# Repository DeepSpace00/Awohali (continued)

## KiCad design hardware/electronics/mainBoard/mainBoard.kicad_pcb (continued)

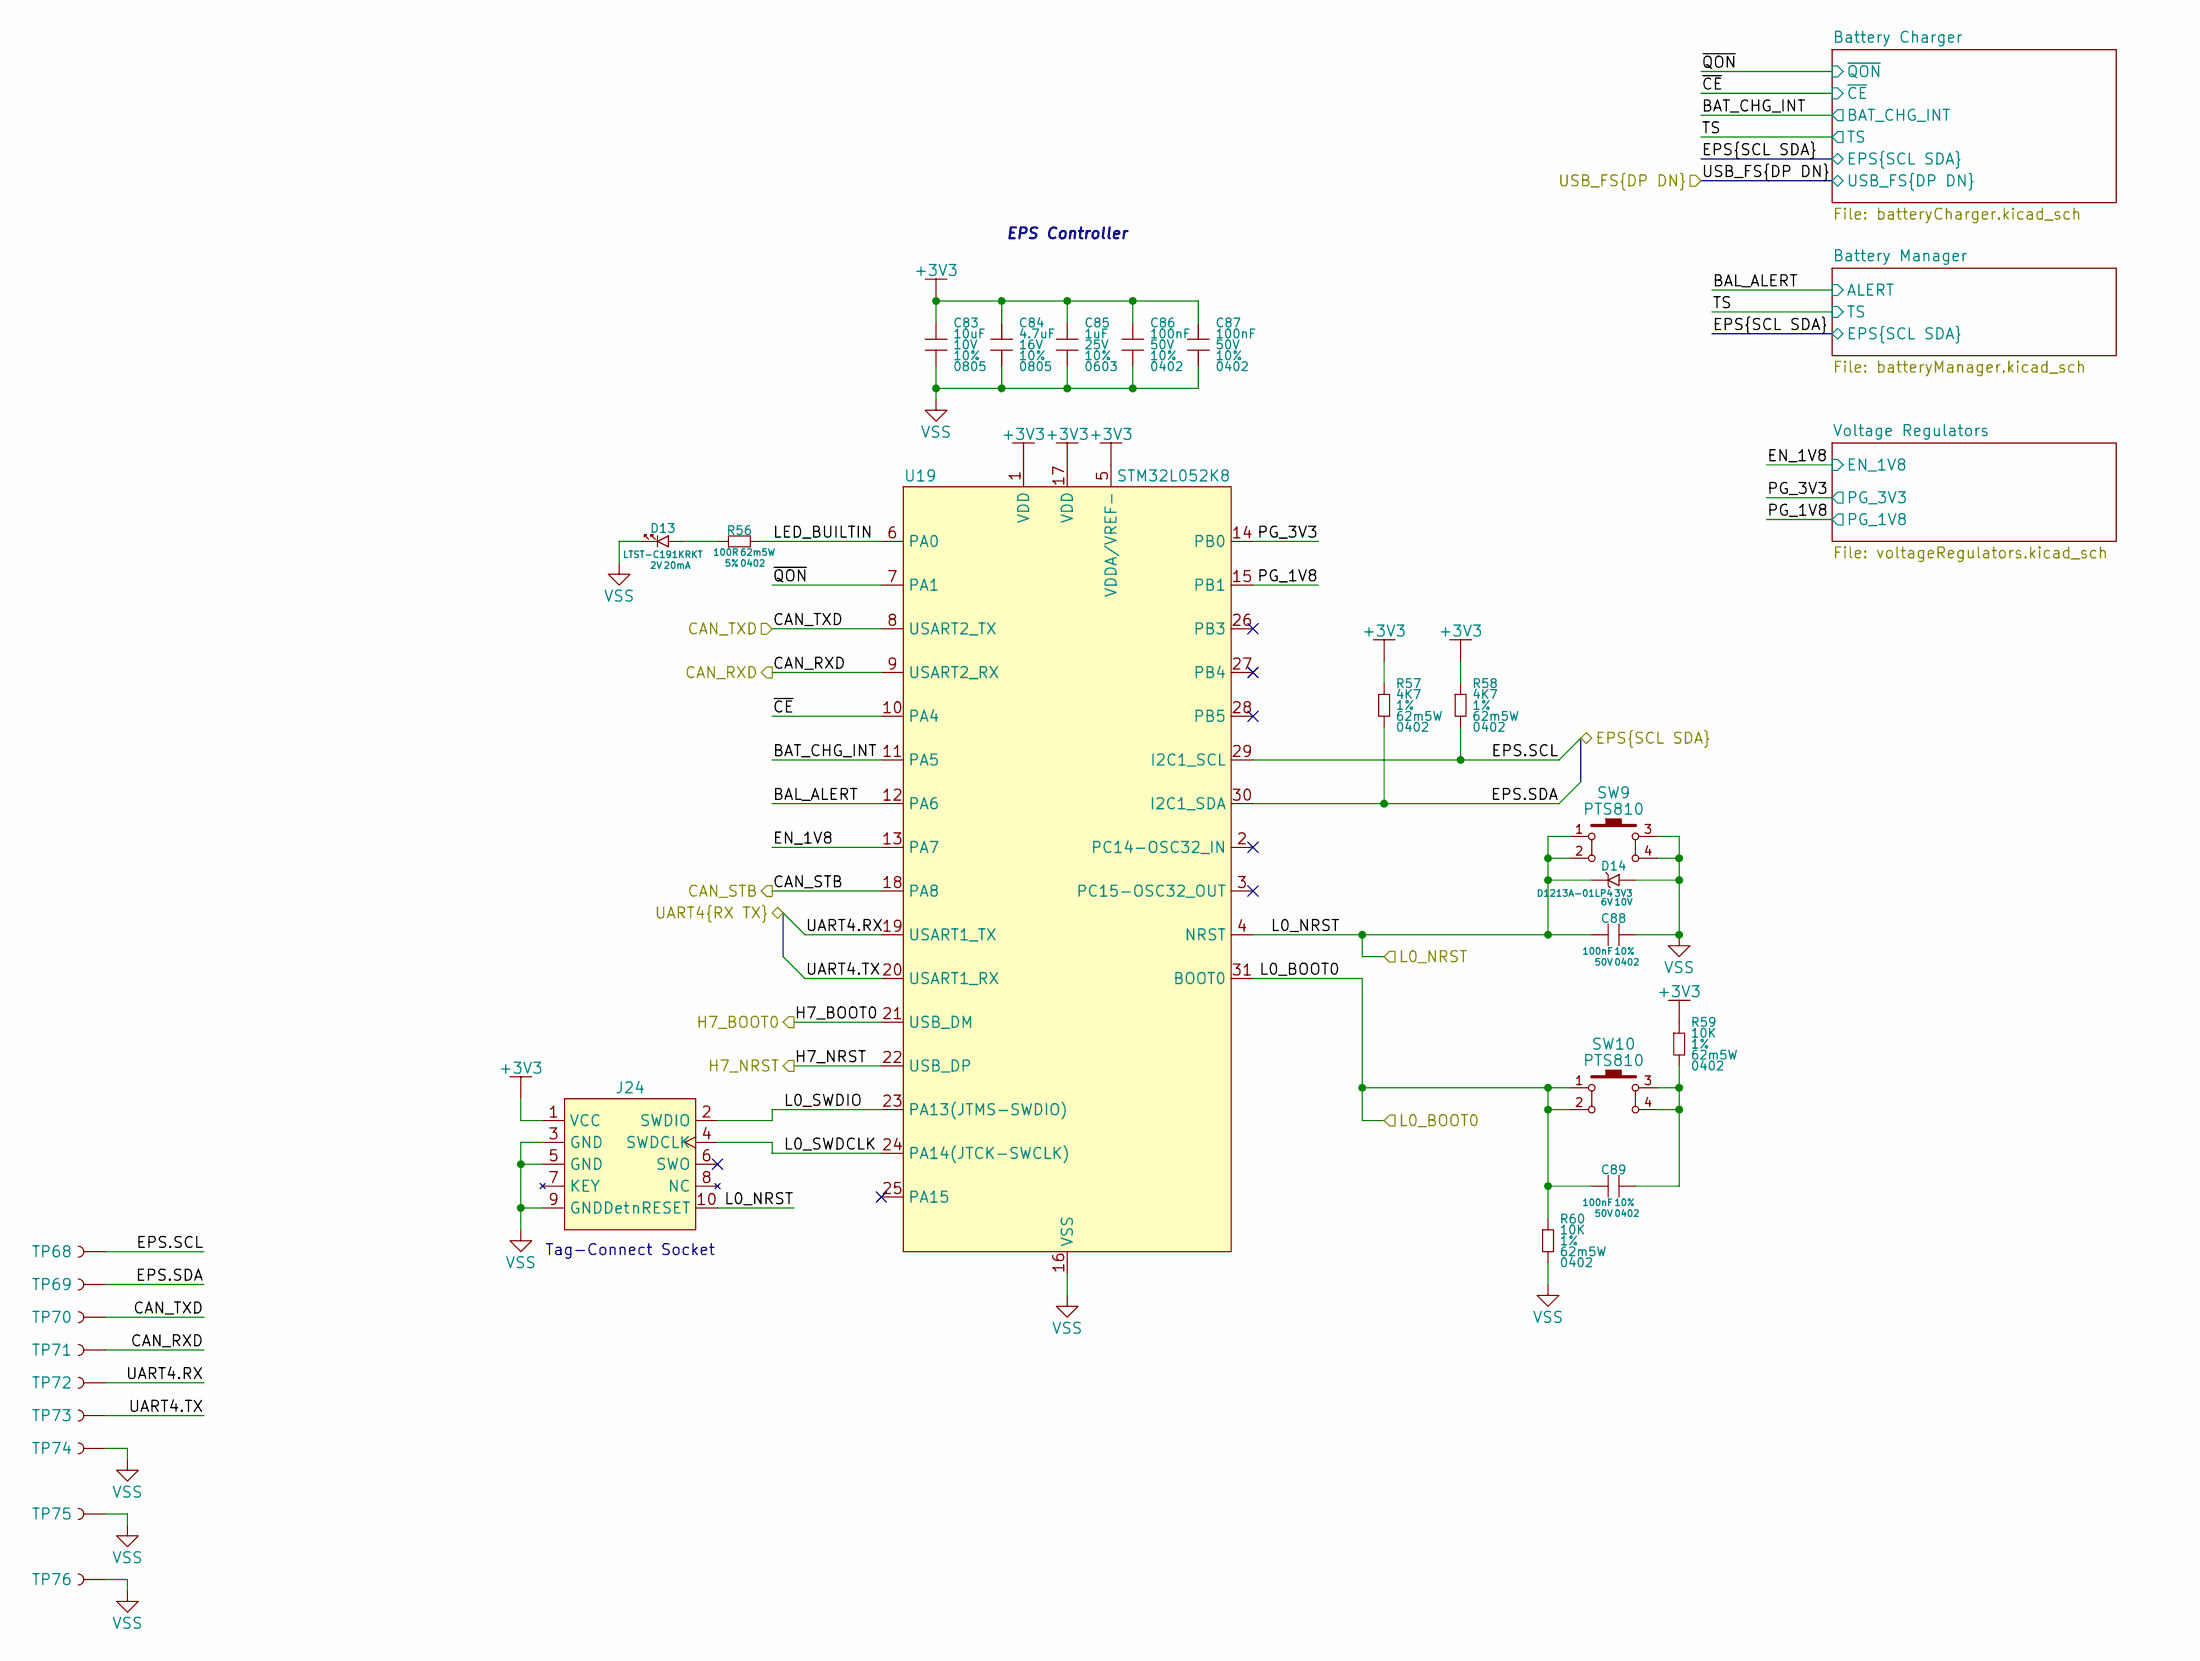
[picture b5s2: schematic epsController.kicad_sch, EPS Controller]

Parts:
C83: 10uF; GCM0805; Tolerance 10%; Voltage Rating 10V; MPN GCM21BR71A106KE22L
C84: 4.7uF; GCM0805; Tolerance 10%; Voltage Rating 16V; MPN GRT21BR71C475KE13L
C85: 1uF; GRT0603; Tolerance 10%; Voltage Rating 25V; MPN GRT188R71E105KE13D
C86, C87: 100nF; GCM0402; Tolerance 10%; Voltage Rating 50V; MPN GRT155R71H104KE01D
C88, C89: 100nF; GCM0402; Voltage Rating 50V; Tolerance 10%; MPN GRT155R71H104KE01D
D13: LTST-C191KRKT; LTST-0603; Forward Voltage 2V; MPN LTST-C191KRKT
D14: D1213A-01LP4; XDFN2P65_100X60X50L50X25L; Voltage - Reverse Stabd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 3V3; Voltage - Breakdown 6V; MPN D1213A-01LP4-7B
J24: TC2050-FP; MPN N/A
R56: 100R; CRCW0402; Tolerance 5%; Power Rating 62m5W; MPN CRCW0402100RJNED
R57, R58: 4K7; CRCW0402; Tolerance 1%; Power Rating 62m5W; MPN CRCW04024K70FKED
R59, R60: 10K; CRCW0402; Tolerance 1%; Power Rating 62m5W; MPN CRCW040210K0FKED
SW9, SW10: PTS810; MPN PTS810SJM250SMTR LFS
TP68, TP69, TP70, TP71, TP72, TP73: TP_2mm; MPN N/A
TP74, TP75, TP76: RCWCTE; TP_RCW; MPN RCWCTE
U19: STM32L052K8; UFQFPN32; MPN STM32L052K6U6TR

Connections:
+3V3: C83.1, C84.1, C85.1, C86.1, C87.1, J24.1 (VCC), R57.1, R58.1, R59.1, U19.1 (VDD), U19.5 (VDDA/VREF-), U19.17 (VDD); also elsewhere on the board
/CAN_RXD: TP71.1, U19.9 (USART2_RX); also elsewhere on the board
/CAN_STB: U19.18 (PA8); also elsewhere on the board
/CAN_TXD: TP70.1, U19.8 (USART2_TX); also elsewhere on the board
/EPS Controller/BAL_ALERT: U19.12 (PA6); also elsewhere on the board
/EPS Controller/BAT_CHG_INT: U19.11 (PA5); also elsewhere on the board
/EPS Controller/EN_1V8: U19.13 (PA7); also elsewhere on the board
/EPS Controller/H7_BOOT0: U19.21 (USB_DM); also elsewhere on the board
/EPS Controller/L0_BOOT0: C89.1, R60.1, SW10.1, SW10.2, U19.31 (BOOT0); also elsewhere on the board
/EPS Controller/L0_NRST: C88.1, D14.1, J24.10 (nRESET), SW9.1, SW9.2, U19.4 (NRST); also elsewhere on the board
/EPS Controller/L0_SWDCLK: J24.4 (SWDCLK), U19.24 (PA14(JTCK-SWCLK))
/EPS Controller/L0_SWDIO: J24.2 (SWDIO), U19.23 (PA13(JTMS-SWDIO))
/EPS Controller/LED_BUILTIN: R56.2, U19.6 (PA0)
/EPS Controller/PG_1V8: U19.15 (PB1); also elsewhere on the board
/EPS Controller/PG_3V3: U19.14 (PB0); also elsewhere on the board
/EPS Controller/UART4.RX: TP72.1, U19.19 (USART1_TX); also elsewhere on the board
/EPS Controller/UART4.TX: TP73.1, U19.20 (USART1_RX); also elsewhere on the board
/EPS Controller/~CE: U19.10 (PA4); also elsewhere on the board
/EPS Controller/~QON: U19.7 (PA1); also elsewhere on the board
/EPS.SCL: R58.2, TP68.1, U19.29 (I2C1_SCL); also elsewhere on the board
/EPS.SDA: R57.2, TP69.1, U19.30 (I2C1_SDA); also elsewhere on the board
/H7_NRST: U19.22 (USB_DP); also elsewhere on the board
unnamed: C89.2, R59.2, SW10.3, SW10.4
unnamed: D13.1, R56.1
VSS: C83.2, C84.2, C85.2, C86.2, C87.2, C88.2, D13.2, D14.2, J24.3 (GND), J24.5 (GND), J24.9 (GNDDet), R60.2, SW9.3, SW9.4, TP74.1, TP75.1, TP76.1, U19.16 (VSS), U19.32 (VSS), U19.33 (VSS); also elsewhere on the board

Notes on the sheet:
Tag-Connect Socket
EPS Controller

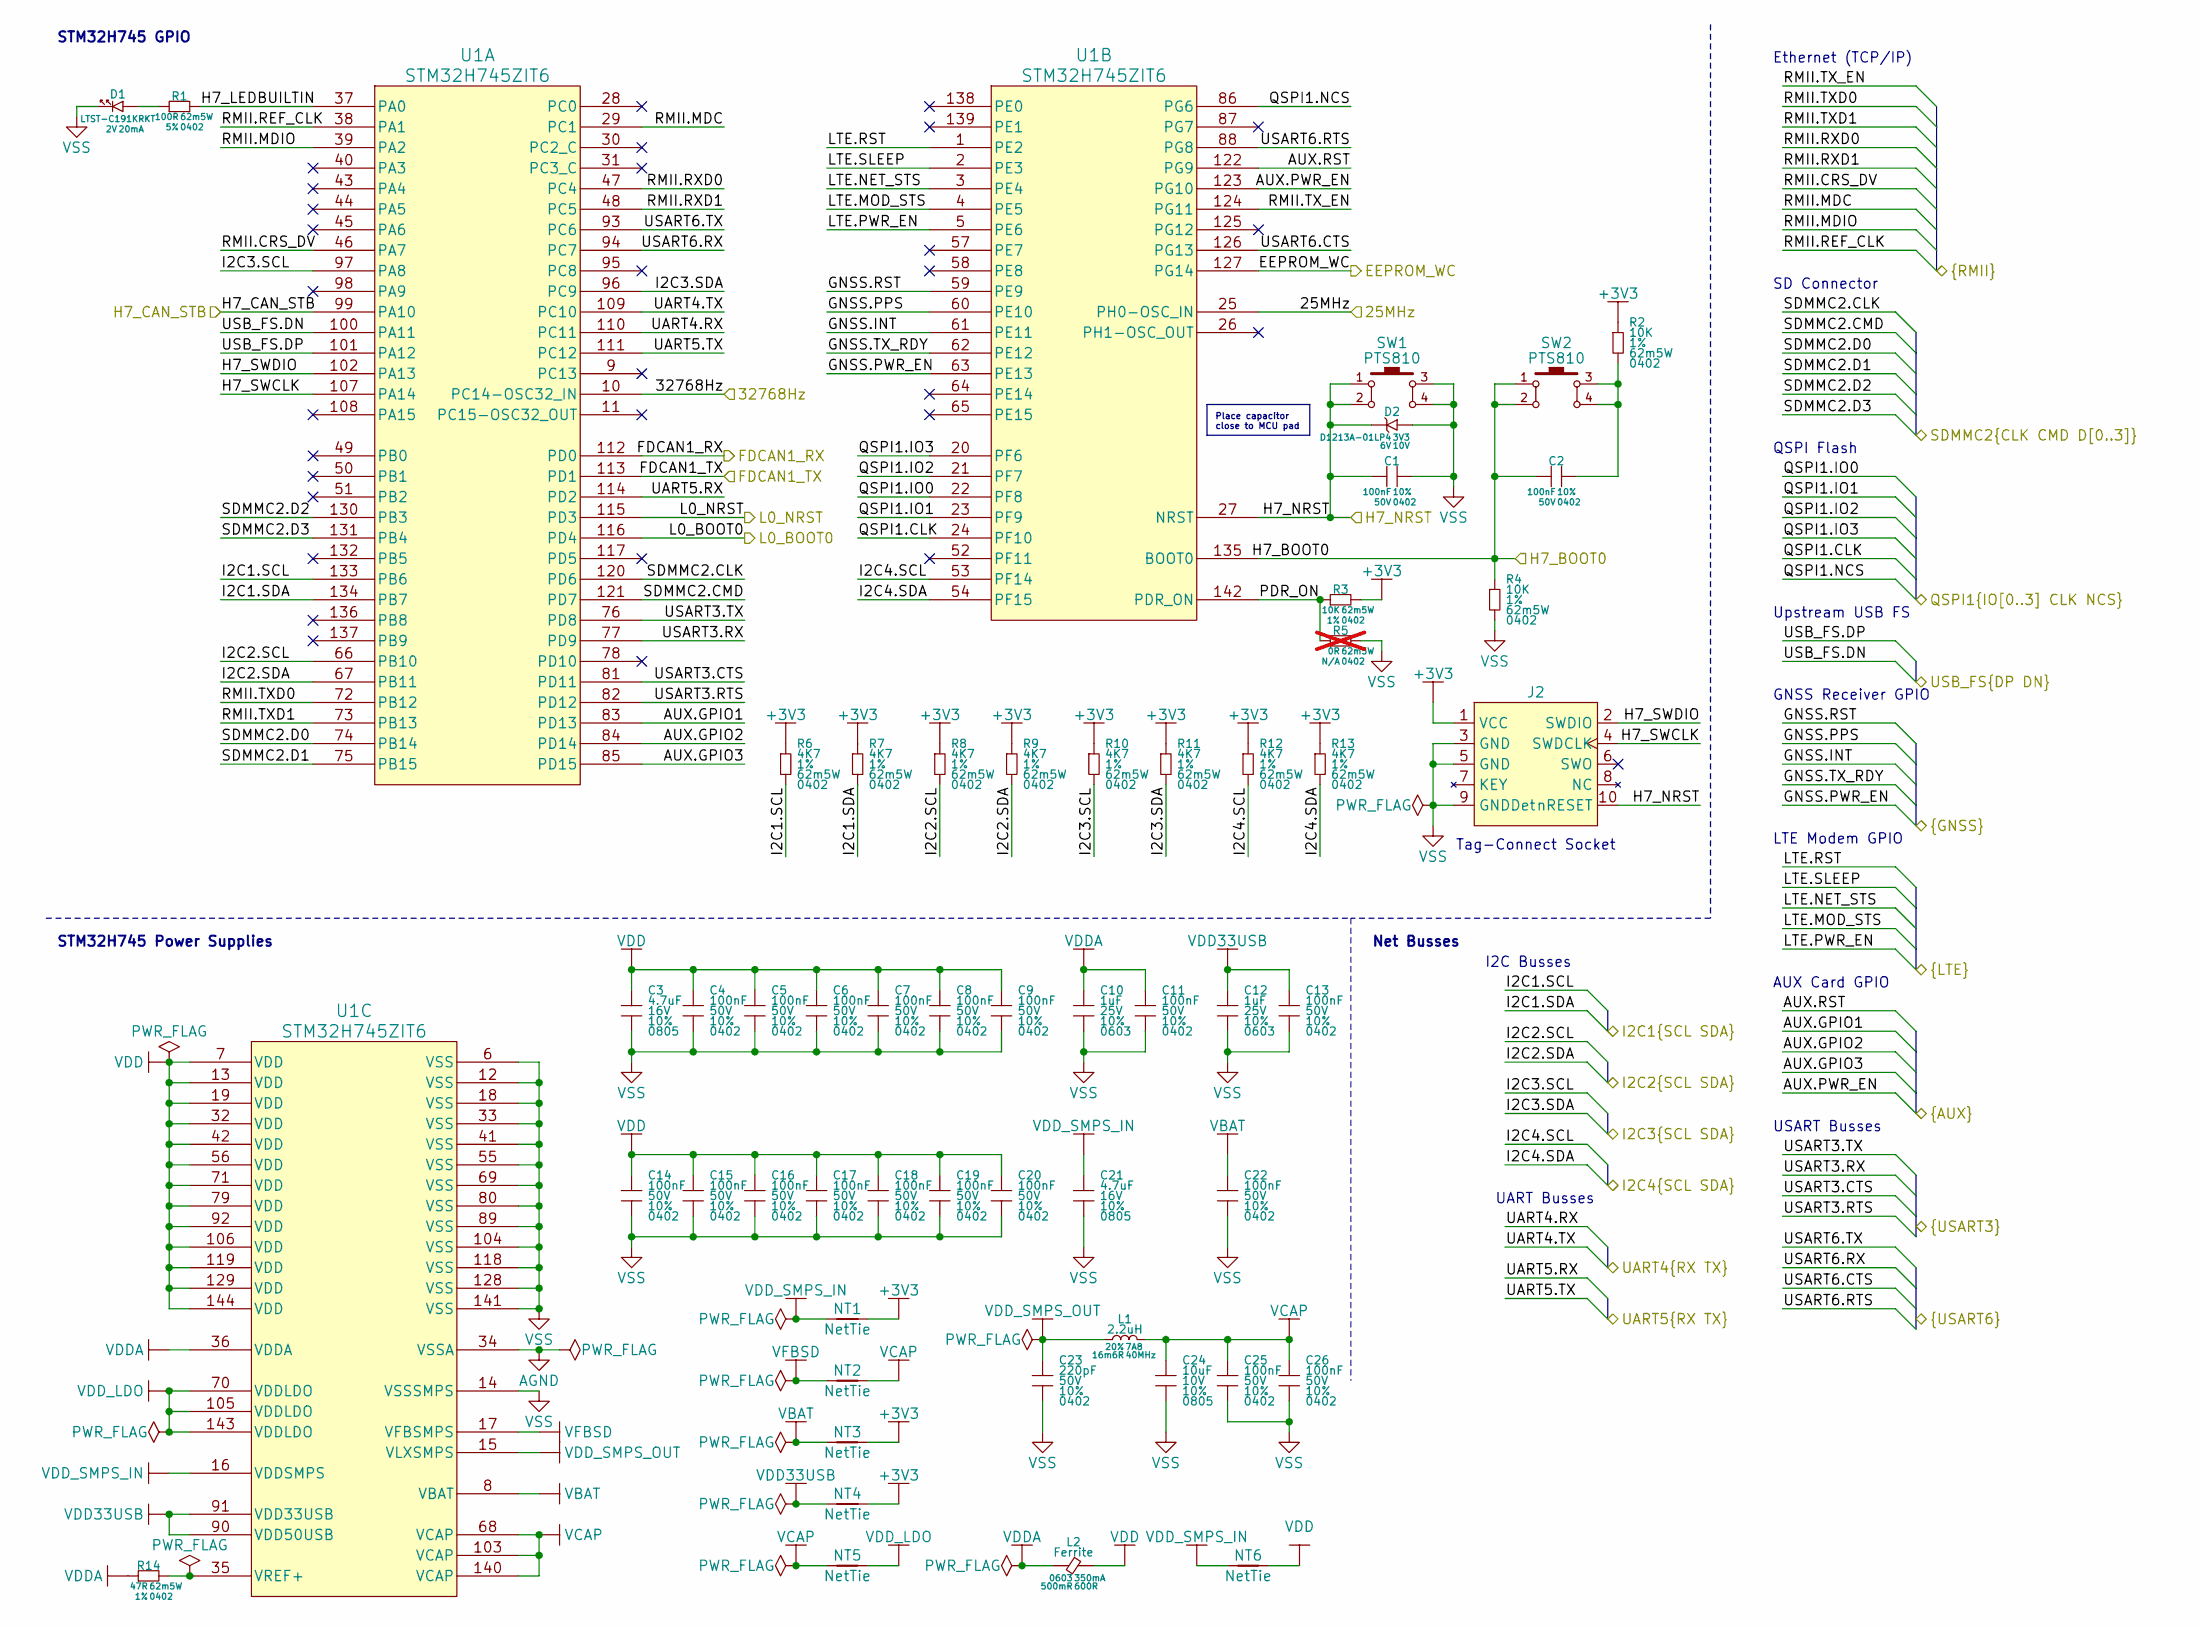
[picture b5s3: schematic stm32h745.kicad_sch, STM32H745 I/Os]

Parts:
C1, C2, C4, C5, C6, C7, C8, C9, C11, C13, C14, C15, C16, C17, C18, C19, C20, C22, C25, C26: 100nF; GCM0402; Tolerance 10%; Voltage Rating 50V; MPN GRT155R71H104KE01D
C3, C21: 4.7uF; GCM0805; Tolerance 10%; Voltage Rating 16V; MPN GRT21BR71C475KE13L
C10, C12: 1uF; GRT0603; Tolerance 10%; Voltage Rating 25V; MPN GRT188R71E105KE13D
C23: 220pF; GCM0402; Tolerance 10%; Voltage Rating 50V; MPN GRT155R71H221KE01D
C24: 10uF; GCM0805; Tolerance 10%; Voltage Rating 10V; MPN GCM21BR71A106KE22L
D1: LTST-C191KRKT; LTST-0603; Forward Voltage 2V; MPN LTST-C191KRKT
D2: D1213A-01LP4; XDFN2P65_100X60X50L50X25L; Voltage - Reverse Stabd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 3V3; Voltage - Breakdown 6V; MPN D1213A-01LP4-7B
J2: TC2050-FP; MPN N/A
L1: 2.2uH; WE-XHMI-4030; Tolerance 20%; Current Rating 7A8; MPN 74439324022
L2: Ferrite; L_0603; Current Rating 350mA; MPN MFBA3V1608K-601-R
NT1, NT2, NT3, NT4, NT5, NT6: NetTie; NetTie-2_SMD_Pad2.0mm
R1: 100R; CRCW0402; Tolerance 5%; Power Rating 62m5W; MPN CRCW0402100RJNED
R2, R3, R4: 10K; CRCW0402; Tolerance 1%; Power Rating 62m5W; MPN CRCW040210K0FKED
R5: 0R; CRCW0402; Tolerance N/A; Power Rating 62m5W; MPN CRCW04020000Z0ED; not fitted
R6, R7, R8, R9, R10, R11, R12, R13: 4K7; CRCW0402; Tolerance 1%; Power Rating 62m5W; MPN CRCW04024K70FKED
R14: 47R; CRCW0402; Tolerance 1%; Power Rating 62m5W; MPN CRCW040247R0FKED
SW1, SW2: PTS810; MPN PTS810SJM250SMTR LFS
U1: STM32H745ZIT6; LQFP-144; MPN STM32H745ZIT6

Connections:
+3V3: J2.1 (VCC), NT1.2, NT3.2, NT4.2, R2.1, R3.2, R6.1, R7.1, R8.1, R9.1, R10.1, R11.1, R12.1, R13.1; also elsewhere on the board
/Auxiliary Card/AUX.GPIO1: U1.83 (PD13); also elsewhere on the board
/Auxiliary Card/AUX.GPIO2: U1.84 (PD14); also elsewhere on the board
/Auxiliary Card/AUX.GPIO3: U1.85 (PD15); also elsewhere on the board
/Auxiliary Card/AUX.PWR_EN: U1.123 (PG10); also elsewhere on the board
/Auxiliary Card/AUX.RST: U1.122 (PG9); also elsewhere on the board
/Auxiliary Card/USART6.CTS: U1.126 (PG13); also elsewhere on the board
/Auxiliary Card/USART6.RTS: U1.88 (PG8); also elsewhere on the board
/Auxiliary Card/USART6.RX: U1.94 (PC7); also elsewhere on the board
/Auxiliary Card/USART6.TX: U1.93 (PC6); also elsewhere on the board
/CANBus Transceivers/FDCAN1_RX: U1.112 (PD0); also elsewhere on the board
/CANBus Transceivers/FDCAN1_TX: U1.113 (PD1); also elsewhere on the board
/CANBus Transceivers/H7_CAN_STB: U1.99 (PA10); also elsewhere on the board
/EPS Controller/H7_BOOT0: C2.1, R4.1, SW2.1, SW2.2, U1.135 (BOOT0); also elsewhere on the board
/EPS Controller/L0_BOOT0: U1.116 (PD4); also elsewhere on the board
/EPS Controller/L0_NRST: U1.115 (PD3); also elsewhere on the board
/EPS Controller/UART4.RX: U1.110 (PC11); also elsewhere on the board
/EPS Controller/UART4.TX: U1.109 (PC10); also elsewhere on the board
/EPS Controller/USB_FS.DN: U1.100 (PA11); also elsewhere on the board
/EPS Controller/USB_FS.DP: U1.101 (PA12); also elsewhere on the board
/Ethernet/RMII.CRS_DV: U1.46 (PA7); also elsewhere on the board
/Ethernet/RMII.MDC: U1.29 (PC1); also elsewhere on the board
/Ethernet/RMII.MDIO: U1.39 (PA2); also elsewhere on the board
/Ethernet/RMII.REF_CLK: U1.38 (PA1); also elsewhere on the board
/Ethernet/RMII.RXD0: U1.47 (PC4); also elsewhere on the board
/Ethernet/RMII.RXD1: U1.48 (PC5); also elsewhere on the board
/Ethernet/RMII.TXD0: U1.72 (PB12); also elsewhere on the board
/Ethernet/RMII.TXD1: U1.73 (PB13); also elsewhere on the board
/Ethernet/RMII.TX_EN: U1.124 (PG11); also elsewhere on the board
/GNSS Card/GNSS.INT: U1.61 (PE11); also elsewhere on the board
/GNSS Card/GNSS.PPS: U1.60 (PE10); also elsewhere on the board
/GNSS Card/GNSS.PWR_EN: U1.63 (PE13); also elsewhere on the board
/GNSS Card/GNSS.RST: U1.59 (PE9); also elsewhere on the board
/GNSS Card/GNSS.TX_RDY: U1.62 (PE12); also elsewhere on the board
/GNSS Card/UART5.RX: U1.114 (PD2); also elsewhere on the board
/GNSS Card/UART5.TX: U1.111 (PC12); also elsewhere on the board
/H7_NRST: C1.1, D2.1, J2.10 (nRESET), SW1.1, SW1.2, U1.27 (NRST); also elsewhere on the board
/I2C1.SCL: R6.2, U1.133 (PB6); also elsewhere on the board
/I2C1.SDA: R7.2, U1.134 (PB7); also elsewhere on the board
/I2C2.SCL: R8.2, U1.66 (PB10); also elsewhere on the board
/I2C2.SDA: R9.2, U1.67 (PB11); also elsewhere on the board
/I2C3.SCL: R10.2, U1.97 (PA8); also elsewhere on the board
/I2C3.SDA: R11.2, U1.96 (PC9); also elsewhere on the board
/I2C4.SCL: R12.2, U1.53 (PF14); also elsewhere on the board
/I2C4.SDA: R13.2, U1.54 (PF15); also elsewhere on the board
/LTE Card/LTE.MOD_STS: U1.4 (PE5); also elsewhere on the board
/LTE Card/LTE.NET_STS: U1.3 (PE4); also elsewhere on the board
/LTE Card/LTE.PWR_EN: U1.5 (PE6); also elsewhere on the board
/LTE Card/LTE.RST: U1.1 (PE2); also elsewhere on the board
/LTE Card/LTE.SLEEP: U1.2 (PE3); also elsewhere on the board
/LTE Card/USART3.CTS: U1.81 (PD11); also elsewhere on the board
/LTE Card/USART3.RTS: U1.82 (PD12); also elsewhere on the board
/LTE Card/USART3.RX: U1.77 (PD9); also elsewhere on the board
/LTE Card/USART3.TX: U1.76 (PD8); also elsewhere on the board
/Memory/EEPROM_WC: U1.127 (PG14); also elsewhere on the board
/Memory/QSPI1.CLK: U1.24 (PF10); also elsewhere on the board
/Memory/QSPI1.IO0: U1.22 (PF8); also elsewhere on the board
/Memory/QSPI1.IO1: U1.23 (PF9); also elsewhere on the board
/Memory/QSPI1.IO2: U1.21 (PF7); also elsewhere on the board
/Memory/QSPI1.IO3: U1.20 (PF6); also elsewhere on the board
/Memory/QSPI1.NCS: U1.86 (PG6); also elsewhere on the board
/Memory/SDMMC2.CLK: U1.120 (PD6); also elsewhere on the board
/Memory/SDMMC2.CMD: U1.121 (PD7); also elsewhere on the board
/Memory/SDMMC2.D0: U1.74 (PB14); also elsewhere on the board
/Memory/SDMMC2.D1: U1.75 (PB15); also elsewhere on the board
/Memory/SDMMC2.D2: U1.130 (PB3); also elsewhere on the board
/Memory/SDMMC2.D3: U1.131 (PB4); also elsewhere on the board
/STM32H745/25MHz: U1.25 (PH0-OSC_IN); also elsewhere on the board
/STM32H745/32768Hz: U1.10 (PC14-OSC32_IN); also elsewhere on the board
/STM32H745/H7_LEDBUILTIN: R1.2, U1.37 (PA0)
/STM32H745/H7_SWCLK: J2.4 (SWDCLK), U1.107 (PA14)
/STM32H745/H7_SWDIO: J2.2 (SWDIO), U1.102 (PA13)
/STM32H745/PDR_ON: R3.1, R5.1, U1.142 (PDR_ON)
AGND: U1.34 (VSSA); also elsewhere on the board
unnamed: C2.2, R2.2, SW2.3, SW2.4
unnamed: D1.1, R1.1
unnamed: R14.2, U1.35 (VREF+)
VBAT: C22.1, NT3.1, U1.8 (VBAT)
VCAP: C24.1, C25.1, C26.1, L1.2, NT2.2, NT5.1, U1.68 (VCAP), U1.103 (VCAP), U1.140 (VCAP)
VDD: C3.1, C4.1, C5.1, C6.1, C7.1, C8.1, C9.1, C14.1, C15.1, C16.1, C17.1, C18.1, C19.1, C20.1, L2.2, NT6.2, U1.7 (VDD), U1.13 (VDD), U1.19 (VDD), U1.32 (VDD), U1.42 (VDD), U1.56 (VDD), U1.71 (VDD), U1.79 (VDD), U1.92 (VDD), U1.106 (VDD), U1.119 (VDD), U1.129 (VDD), U1.144 (VDD)
VDD33USB: C12.1, C13.1, NT4.1, U1.90 (VDD50USB), U1.91 (VDD33USB)
VDDA: C10.1, C11.1, L2.1, R14.1, U1.36 (VDDA)
VDD_LDO: NT5.2, U1.70 (VDDLDO), U1.105 (VDDLDO), U1.143 (VDDLDO)
VDD_SMPS_IN: C21.1, NT1.1, NT6.1, U1.16 (VDDSMPS)
VDD_SMPS_OUT: C23.1, L1.1, U1.15 (VLXSMPS)
VFBSD: NT2.1, U1.17 (VFBSMPS)
VSS: C1.2, C3.2, C4.2, C5.2, C6.2, C7.2, C8.2, C9.2, C10.2, C11.2, C12.2, C13.2, C14.2, C15.2, C16.2, C17.2, C18.2, C19.2, C20.2, C21.2, C22.2, C23.2, C24.2, C25.2, C26.2, D1.2, D2.2, J2.3 (GND), J2.5 (GND), J2.9 (GNDDet), R4.2, R5.2, SW1.3, SW1.4, U1.6 (VSS), U1.12 (VSS), U1.14 (VSSSMPS), U1.18 (VSS), U1.33 (VSS), U1.41 (VSS), U1.55 (VSS), U1.69 (VSS), U1.80 (VSS), U1.89 (VSS), U1.104 (VSS), U1.118 (VSS), U1.128 (VSS), U1.141 (VSS); also elsewhere on the board

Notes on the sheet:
I2C Busses
USART Busses
UART Busses
GNSS Receiver GPIO
Ethernet (TCP/IP)
Tag-Connect Socket
QSPI Flash
SD Connector
AUX Card GPIO
Net Busses
STM32H745 GPIO
STM32H745 Power Supplies
Upstream USB FS
LTE Modem GPIO
Place capacitor close to MCU pad

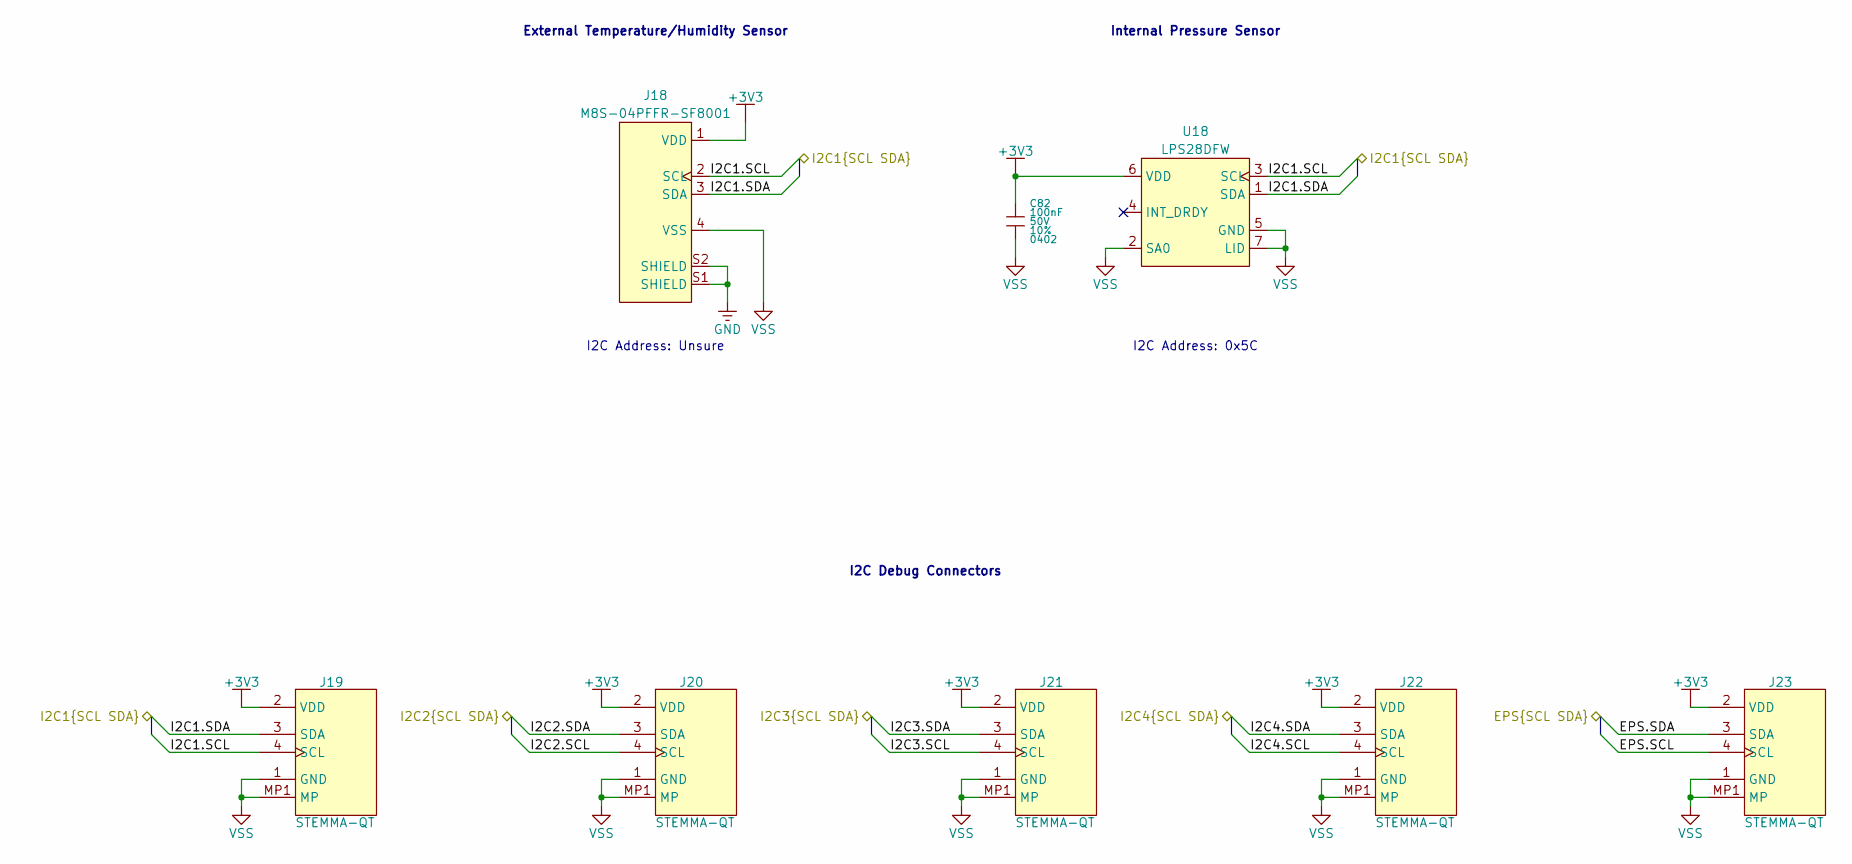
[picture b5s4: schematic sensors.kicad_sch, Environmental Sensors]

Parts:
C82: 100nF; GCM0402; Tolerance 10%; Voltage Rating 50V; MPN GRT155R71H104KE01D
J18: M8S-04PFFR-SF8001; MPN M8S-04PFFR-SF8001
J19, J20, J21, J22, J23: STEMMA-QT; JST_SH_BM04B-SRSS-TB; MPN BM04B-SRSS-TB
U18: LPS28DFW; CCLGA7_LPS28DFWTR; MPN LPS28DFWTR

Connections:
+3V3: C82.1, J18.1 (VDD), J19.2 (VDD), J20.2 (VDD), J21.2 (VDD), J22.2 (VDD), J23.2 (VDD), U18.6 (VDD); also elsewhere on the board
/EPS.SCL: J23.4 (SCL); also elsewhere on the board
/EPS.SDA: J23.3 (SDA); also elsewhere on the board
/I2C1.SCL: J18.2 (SCL), J19.4 (SCL), U18.3 (SCL); also elsewhere on the board
/I2C1.SDA: J18.3 (SDA), J19.3 (SDA), U18.1 (SDA); also elsewhere on the board
/I2C2.SCL: J20.4 (SCL); also elsewhere on the board
/I2C2.SDA: J20.3 (SDA); also elsewhere on the board
/I2C3.SCL: J21.4 (SCL); also elsewhere on the board
/I2C3.SDA: J21.3 (SDA); also elsewhere on the board
/I2C4.SCL: J22.4 (SCL); also elsewhere on the board
/I2C4.SDA: J22.3 (SDA); also elsewhere on the board
GND: J18.S1 (SHIELD), J18.S2 (SHIELD); also elsewhere on the board
VSS: C82.2, J18.4 (VSS), J19.1 (GND), J19.MP1 (MP), J19.MP2 (MP), J20.1 (GND), J20.MP1 (MP), J20.MP2 (MP), J21.1 (GND), J21.MP1 (MP), J21.MP2 (MP), J22.1 (GND), J22.MP1 (MP), J22.MP2 (MP), J23.1 (GND), J23.MP1 (MP), J23.MP2 (MP), U18.2 (SA0), U18.5 (GND), U18.7 (LID); also elsewhere on the board

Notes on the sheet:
I2C Address: Unsure
I2C Address: 0x5C
Internal Pressure Sensor
I2C Debug Connectors
External Temperature/Humidity Sensor

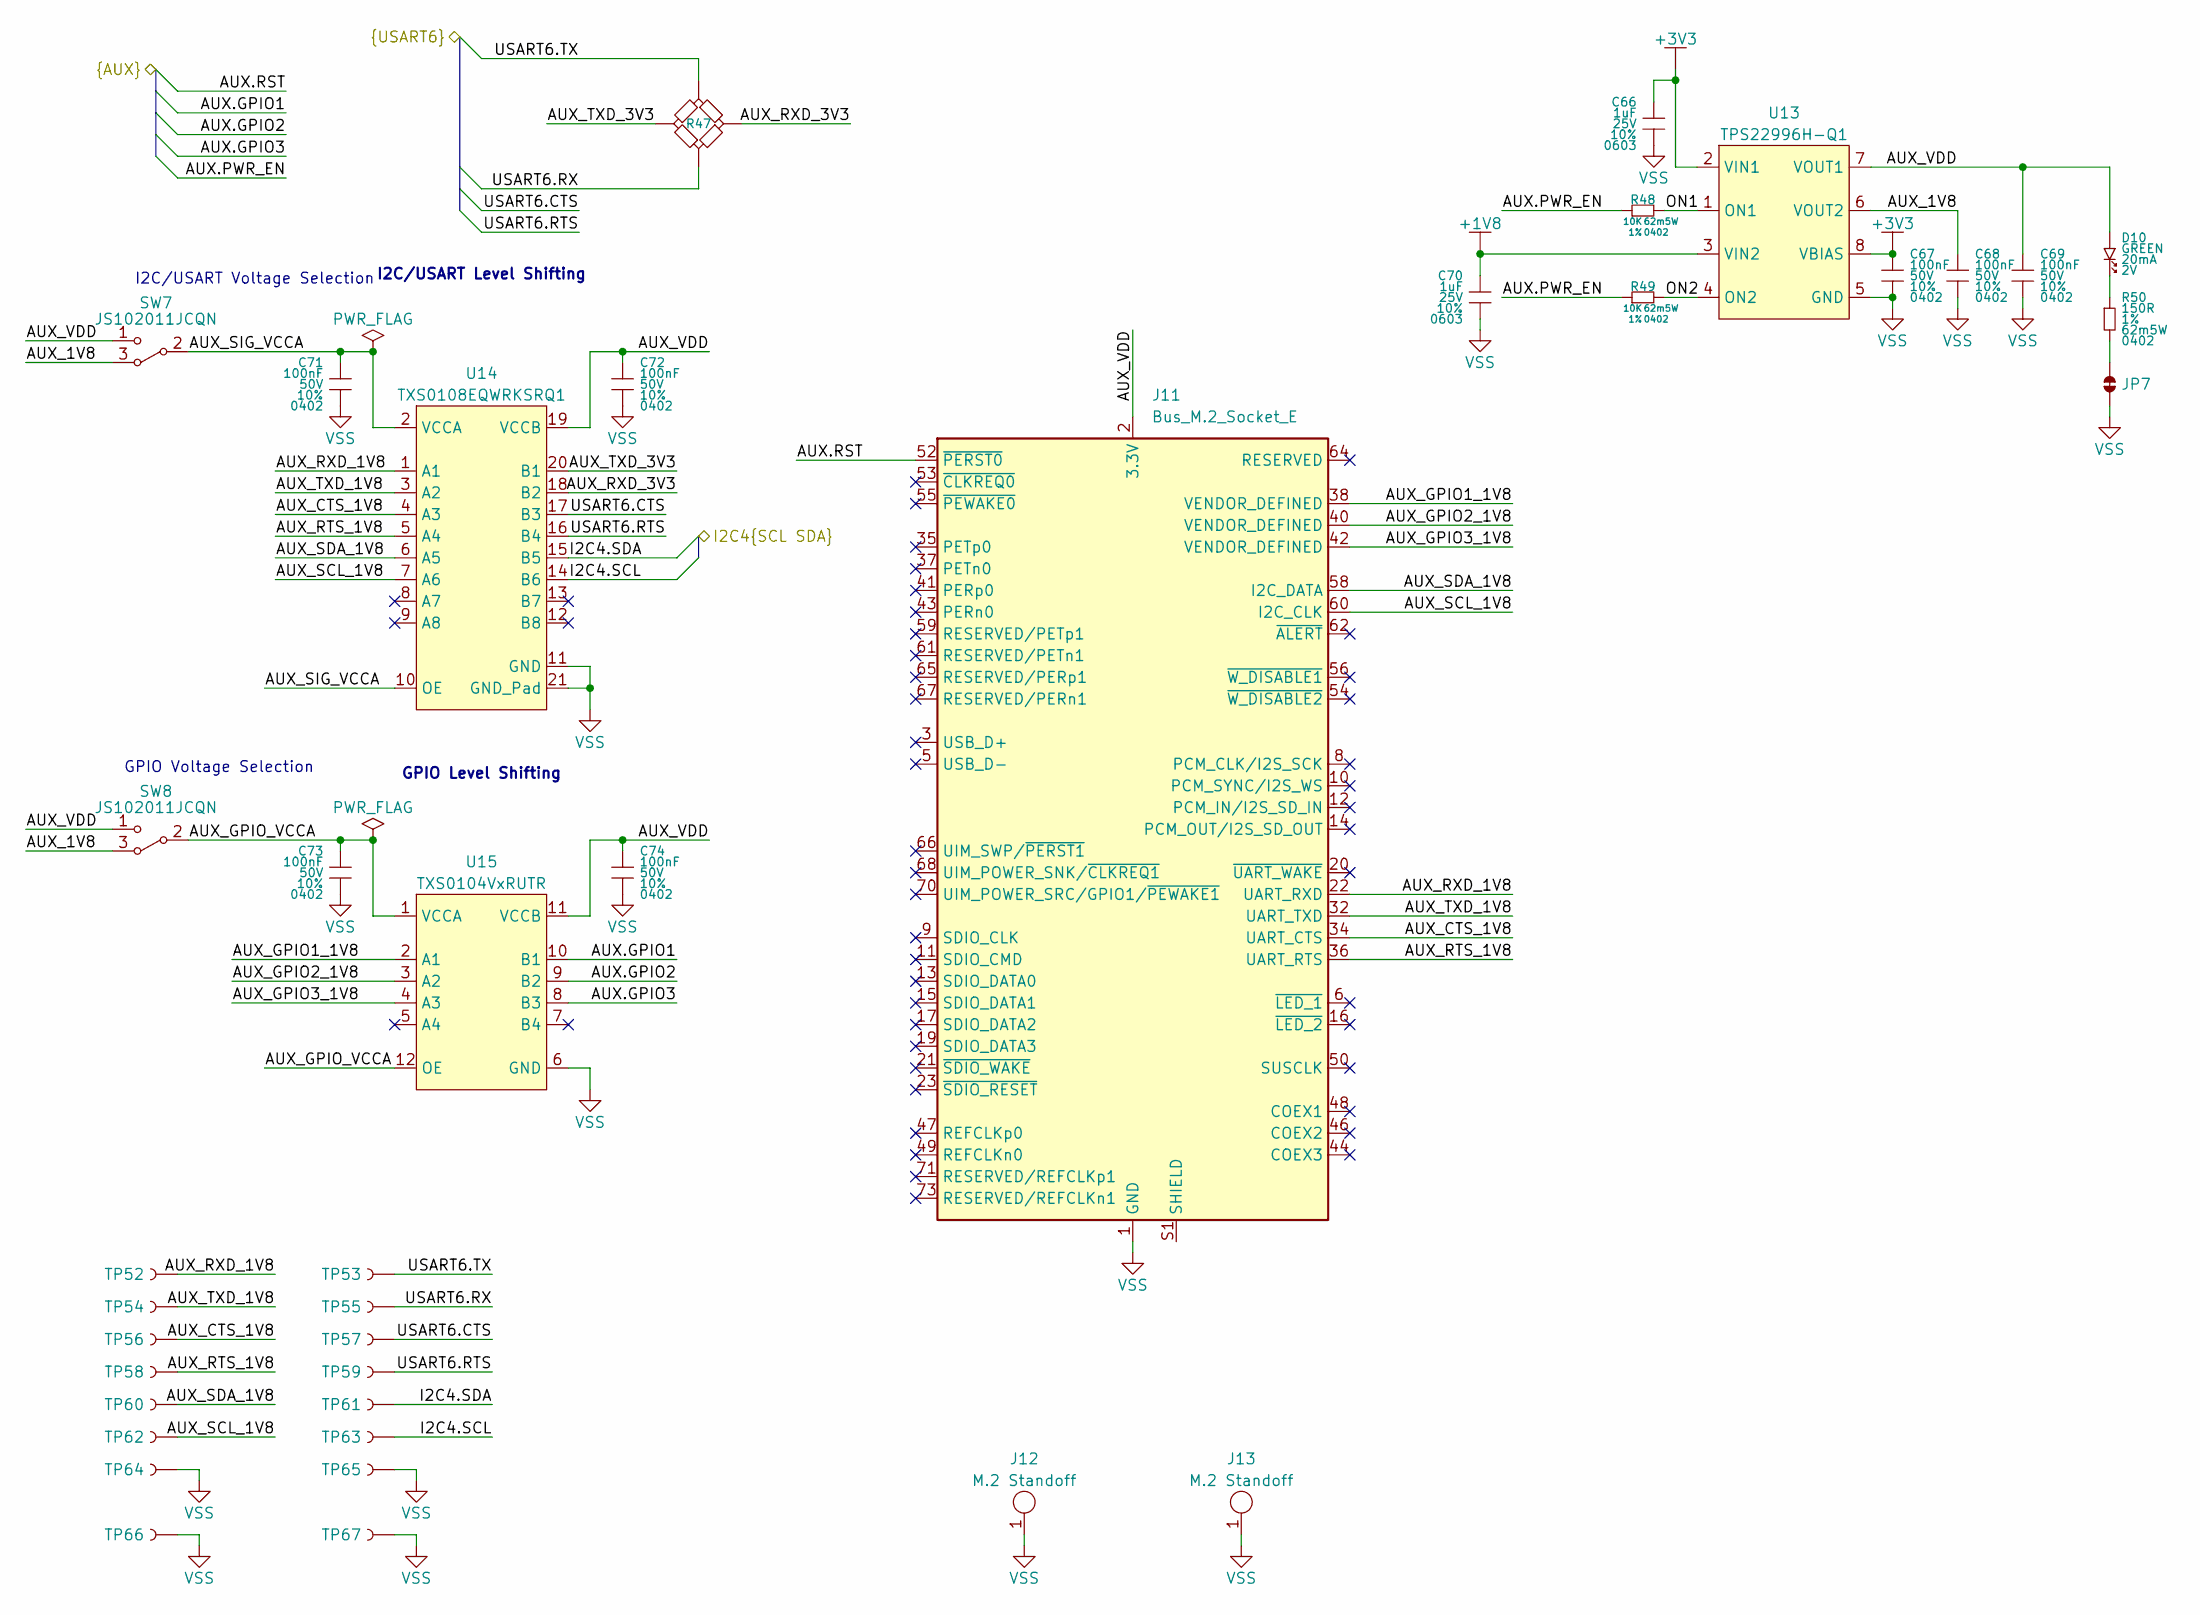
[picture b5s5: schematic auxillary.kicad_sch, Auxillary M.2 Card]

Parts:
C66, C70: 1uF; GRT0603; Tolerance 10%; Voltage Rating 25V; MPN GRT188R71E105KE13D
C67, C68, C69, C71, C72, C73, C74: 100nF; GCM0402; Tolerance 10%; Voltage Rating 50V; MPN GRT155R71H104KE01D
D10: LTST-C191KGKT; LTST-0603; Forward Voltage 2V; MPN LTST-C191KGKT
J11: Bus_M.2_Socket_E; MDT420E01001; MPN MDT420E01001
J12, J13: M.2 Standoff; MountingHole_3.5mm_Pad_Via; MPN 123A-NUT-42
JP7: SolderJumper-2_P1.3mm_Bridged_RoundedPad1.0x1.5mm
R47: CRCW0402_QUAD_UART
R48, R49: 10K; CRCW0402; Tolerance 1%; Power Rating 62m5W; MPN CRCW040210K0FKED
R50: 150R; CRCW0402; Tolerance 1%; Power Rating 62m5W; MPN CRCW0402150RFKED
SW7, SW8: JS102011JCQN; MPN C&K
TP52, TP53, TP54, TP55, TP56, TP57, TP58, TP59, TP60, TP61, TP62, TP63: TP_2mm; MPN N/A
TP64, TP65, TP66, TP67: RCWCTE; TP_RCW; MPN RCWCTE
U13: TPS22996H-Q1; SOT583; MPN TPS22996HQDYCRQ1
U14: TXS0108EQWRKSRQ1; QFN50P450X250X100-20; MPN TXS0108EQWRKSRQ1
U15: TXS0104VxRUTR; QFN40P170X200X55-12; MPN TXS0104VQRUTRQ1

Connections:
+1V8: C70.1, U13.3 (VIN2); also elsewhere on the board
+3V3: C66.1, C67.1, U13.2 (VIN1), U13.8 (VBIAS); also elsewhere on the board
/Auxiliary Card/AUX.GPIO1: U15.10 (B1); also elsewhere on the board
/Auxiliary Card/AUX.GPIO2: U15.9 (B2); also elsewhere on the board
/Auxiliary Card/AUX.GPIO3: U15.8 (B3); also elsewhere on the board
/Auxiliary Card/AUX.PWR_EN: R48.1, R49.1; also elsewhere on the board
/Auxiliary Card/AUX.RST: J11.52 (~PERST0); also elsewhere on the board
/Auxiliary Card/AUX_1V8: C68.1, SW7.3, SW8.3, U13.6 (VOUT2)
/Auxiliary Card/AUX_CTS_1V8: J11.34 (UART_CTS), TP56.1, U14.4 (A3)
/Auxiliary Card/AUX_GPIO1_1V8: J11.38 (VENDOR_DEFINED), U15.2 (A1)
/Auxiliary Card/AUX_GPIO2_1V8: J11.40 (VENDOR_DEFINED), U15.3 (A2)
/Auxiliary Card/AUX_GPIO3_1V8: J11.42 (VENDOR_DEFINED), U15.4 (A3)
/Auxiliary Card/AUX_GPIO_VCCA: C73.1, SW8.2, U15.1 (VCCA), U15.12 (OE)
/Auxiliary Card/AUX_RTS_1V8: J11.36 (UART_RTS), TP58.1, U14.5 (A4)
/Auxiliary Card/AUX_RXD_1V8: J11.22 (UART_RXD), TP52.1, U14.1 (A1)
/Auxiliary Card/AUX_RXD_3V3: R47.2, U14.18 (B2)
/Auxiliary Card/AUX_SCL_1V8: J11.60 (I2C_CLK), TP62.1, U14.7 (A6)
/Auxiliary Card/AUX_SDA_1V8: J11.58 (I2C_DATA), TP60.1, U14.6 (A5)
/Auxiliary Card/AUX_SIG_VCCA: C71.1, SW7.2, U14.2 (VCCA), U14.10 (OE)
/Auxiliary Card/AUX_TXD_1V8: J11.32 (UART_TXD), TP54.1, U14.3 (A2)
/Auxiliary Card/AUX_TXD_3V3: R47.4, U14.20 (B1)
/Auxiliary Card/AUX_VDD: C69.1, C72.1, C74.1, D10.1, J11.2 (3.3V), J11.4 (3.3V), J11.72 (3.3V), J11.74 (3.3V), SW7.1, SW8.1, U13.7 (VOUT1), U14.19 (VCCB), U15.11 (VCCB)
/Auxiliary Card/ON1: R48.2, U13.1 (ON1)
/Auxiliary Card/ON2: R49.2, U13.4 (ON2)
/Auxiliary Card/USART6.CTS: TP57.1, U14.17 (B3); also elsewhere on the board
/Auxiliary Card/USART6.RTS: TP59.1, U14.16 (B4); also elsewhere on the board
/Auxiliary Card/USART6.RX: R47.3, TP55.1; also elsewhere on the board
/Auxiliary Card/USART6.TX: R47.1, TP53.1; also elsewhere on the board
/I2C4.SCL: TP63.1, U14.14 (B6); also elsewhere on the board
/I2C4.SDA: TP61.1, U14.15 (B5); also elsewhere on the board
unnamed: D10.2, R50.1
unnamed: J11.S1 (SHIELD), J11.S2 (SHIELD)
unnamed: JP7.1, R50.2
VSS: C66.2, C67.2, C68.2, C69.2, C70.2, C71.2, C72.2, C73.2, C74.2, J11.1 (GND), J11.7 (GND), J11.18 (GND), J11.33 (GND), J11.39 (GND), J11.45 (GND), J11.51 (GND), J11.57 (GND), J11.63 (GND), J11.69 (GND), J11.75 (GND), J12.1, J13.1, JP7.2, TP64.1, TP65.1, TP66.1, TP67.1, U13.5 (GND), U14.11 (GND), U14.21 (GND_Pad), U15.6 (GND); also elsewhere on the board

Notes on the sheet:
GPIO Voltage Selection
I2C/USART Level Shifting
I2C/USART Voltage Selection
GPIO Level Shifting
